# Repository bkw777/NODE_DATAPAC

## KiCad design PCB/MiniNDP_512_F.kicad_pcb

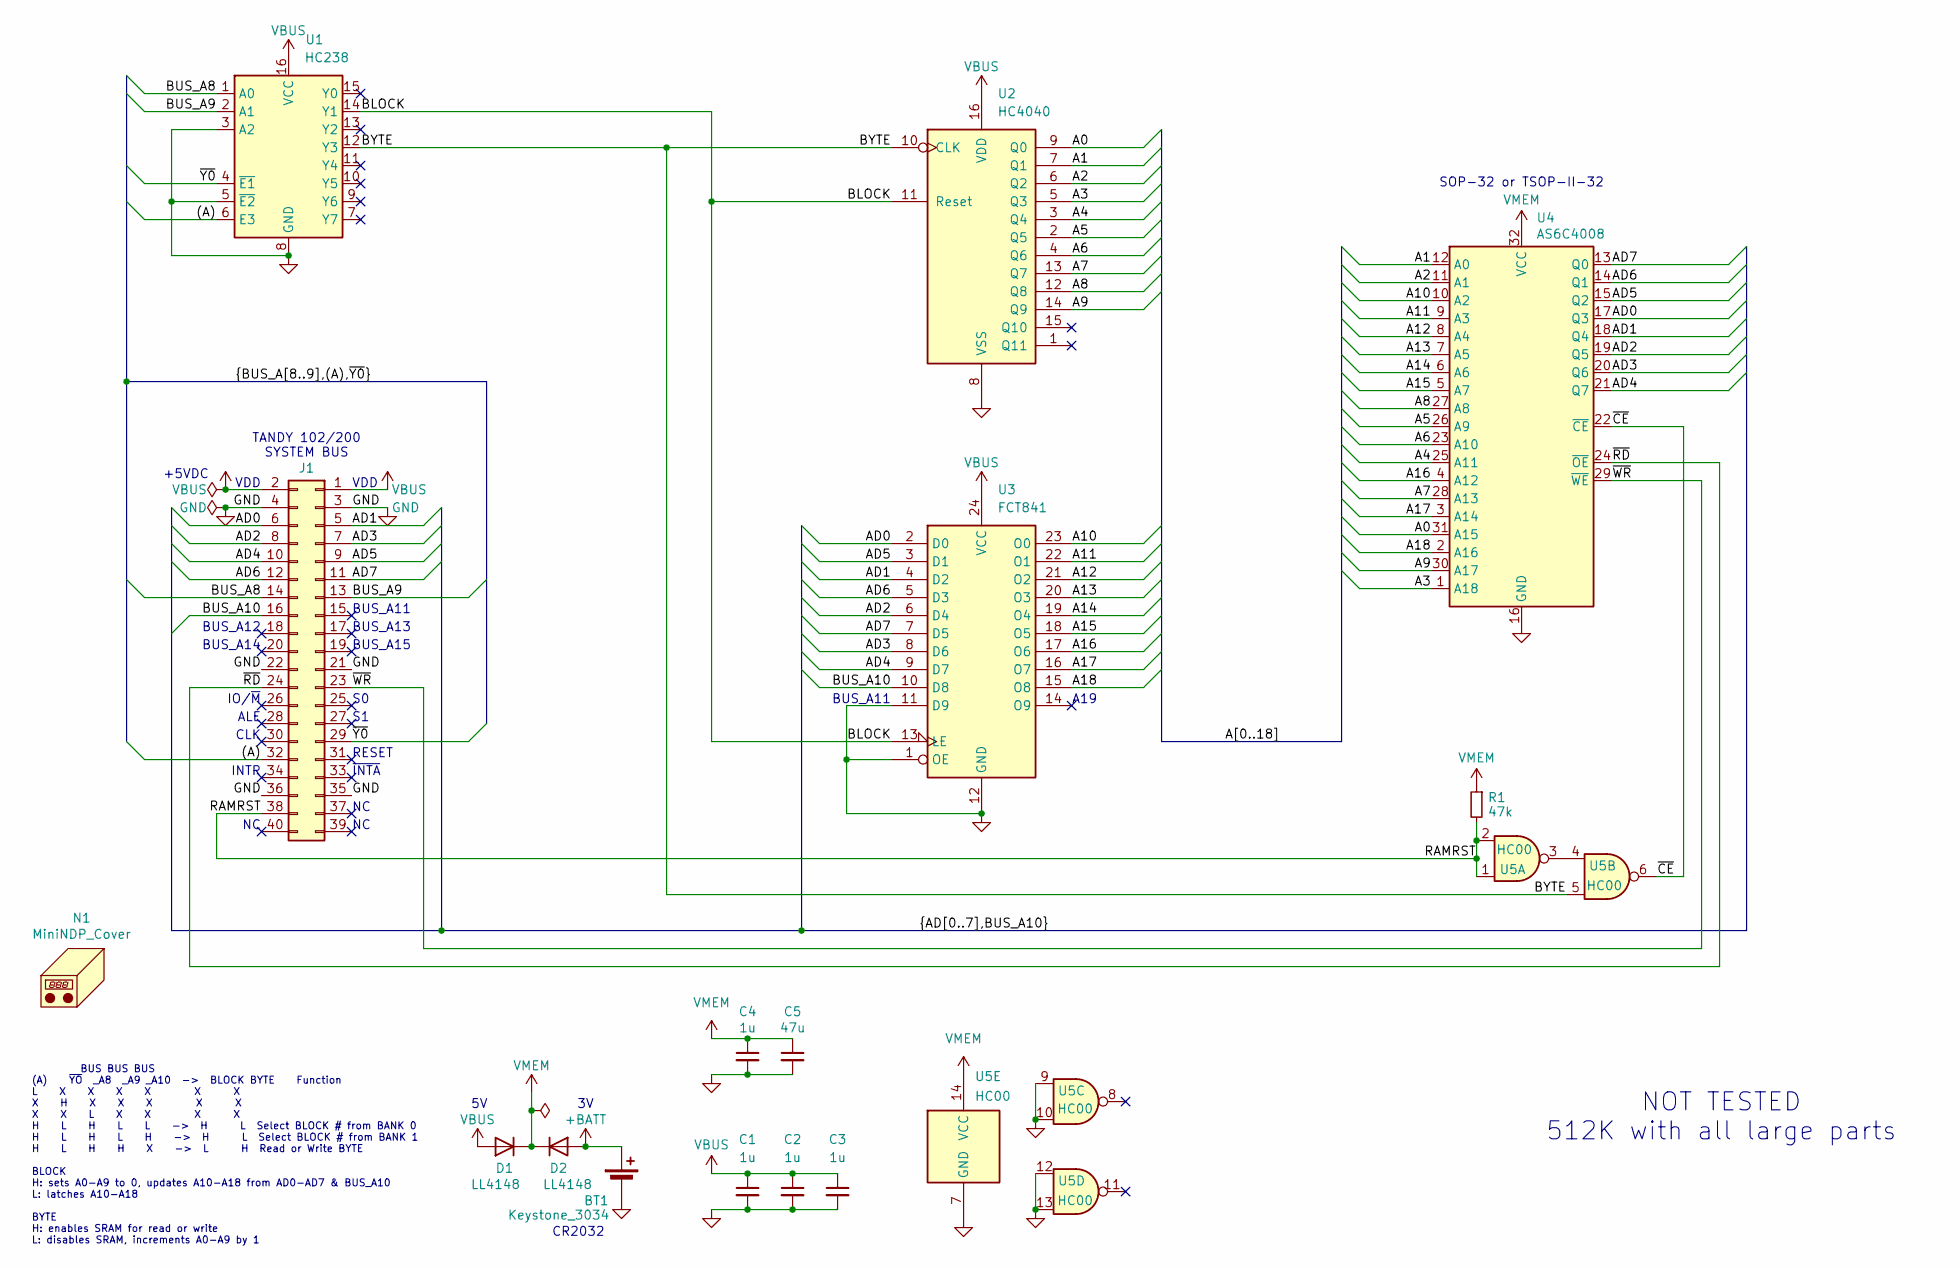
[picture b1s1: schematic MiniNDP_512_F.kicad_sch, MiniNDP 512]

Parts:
BT1: Keystone_3034; Keystone_3028_3034; MPN Keystone 3034
C1, C2, C3, C4: 1u; C_1206; MPN CL31B105KAHNNNE
C5: 47u; C_1206; MPN C3216X5R1E476M160DC
D1, D2: LL4148; D_MiniMELF; MPN FDLL4148
J1: Conn_02x20_Odd_Even; IDC-Header_2x20_P2.54mm_Vertical; MPN 302-S401
N1: MiniNDP_Cover; MPN MiniNDP_Cover.stl
R1: 47k; R_1206; MPN CRGCQ1206F47K
U1: HC238; SOIC-16_3.9x9.9mm_P1.27mm; MPN 74HCT238D,653
U2: HC4040; SOIC-16_3.9x9.9mm_P1.27mm; MPN 74HC4040D,653
U3: FCT841; SOIC-24; MPN CY74FCT841CTSOC
U4: AS6C4008; TSOP-II-SOP-32_dual; MPN AS6C4008-55ZIN
U5: HC00; SOIC-14_3.9x8.7mm_P1.27mm; MPN 74HC00D,653

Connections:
+BATT: BT1.1 (+), D2.2 (A)
/(A): J1.32, U1.6 (E3)
/A0: U2.9 (Q0), U4.31 (A15)
/A1: U2.7 (Q1), U4.12 (A0)
/A2: U2.6 (Q2), U4.11 (A1)
/A3: U2.5 (Q3), U4.1 (A18)
/A4: U2.3 (Q4), U4.25 (A11)
/A5: U2.2 (Q5), U4.26 (A9)
/A6: U2.4 (Q6), U4.23 (A10)
/A7: U2.13 (Q7), U4.28 (A13)
/A8: U2.12 (Q8), U4.27 (A8)
/A9: U2.14 (Q9), U4.30 (A17)
/A10: U3.23 (O0), U4.10 (A2)
/A11: U3.22 (O1), U4.9 (A3)
/A12: U3.21 (O2), U4.8 (A4)
/A13: U3.20 (O3), U4.7 (A5)
/A14: U3.19 (O4), U4.6 (A6)
/A15: U3.18 (O5), U4.5 (A7)
/A16: U3.17 (O6), U4.4 (A12)
/A17: U3.16 (O7), U4.3 (A14)
/A18: U3.15 (O8), U4.2 (A16)
/AD0: J1.6, U3.2 (D0), U4.17 (Q3)
/AD1: J1.5, U3.4 (D2), U4.18 (Q4)
/AD2: J1.8, U3.6 (D4), U4.19 (Q5)
/AD3: J1.7, U3.8 (D6), U4.20 (Q6)
/AD4: J1.10, U3.9 (D7), U4.21 (Q7)
/AD5: J1.9, U3.3 (D1), U4.15 (Q2)
/AD6: J1.12, U3.5 (D3), U4.14 (Q1)
/AD7: J1.11, U3.7 (D5), U4.13 (Q0)
/BLOCK: U1.14 (Y1), U2.11 (Reset), U3.13 (LE)
/BUS_A8: J1.14, U1.1 (A0)
/BUS_A9: J1.13, U1.2 (A1)
/BUS_A10: J1.16, U3.10 (D8)
/BYTE: U1.12 (Y3), U2.10 (CLK), U5.5
/RAMRST: J1.38, R1.2, U5.1, U5.2
/~CE: U4.22 (~CE), U5.6
/~RD: J1.24, U4.24 (~OE)
/~WR: J1.23, U4.29 (~WE)
/~Y0: J1.29, U1.4 (~E1)
GND: BT1.2 (-), C1.2, C2.2, C3.2, C4.2, C5.2, J1.3, J1.4, J1.21, J1.22, J1.35, J1.36, U1.3 (A2), U1.5 (~E2), U1.8 (GND), U2.8 (VSS), U3.1 (OE), U3.11 (D9), U3.12 (GND), U4.16 (GND), U5.7 (GND), U5.9, U5.10, U5.12, U5.13
unnamed: U5.3, U5.4
VBUS: C1.1, C2.1, C3.1, D1.2 (A), J1.1, J1.2, U1.16 (VCC), U2.16 (VDD), U3.24 (VCC)
VMEM: C4.1, C5.1, D1.1 (K), D2.1 (K), R1.1, U4.32 (VCC), U5.14 (VCC)

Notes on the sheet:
BUS_A11
TANDY 102/200 SYSTEM BUS
+5VDC
BUS_A15
NOT TESTED 512K with all large parts
INTR
BUS_A14
ALE
SOP-32 or TSOP-II-32
~{INTA}
CR2032
CLK
IO/~{M}
VDD
RESET
A19
BUS_A13
BUS BUS BUS (A) ~{YO} _A8 _A9 _A10 -> BLOCK BYTE Function L X X X X X X X H X X X X X X X L X X X X H L H L L -> H L Select BLOCK # from BANK 0 H L H L H -> H L Select BLOCK # from BANK 1 H L H H X -> L H Read or Write BYTE BLOCK H: sets A0-A9 to 0, updates A10-A18 from AD0-AD7 & BUS_A10 L: latches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
BUS_A12

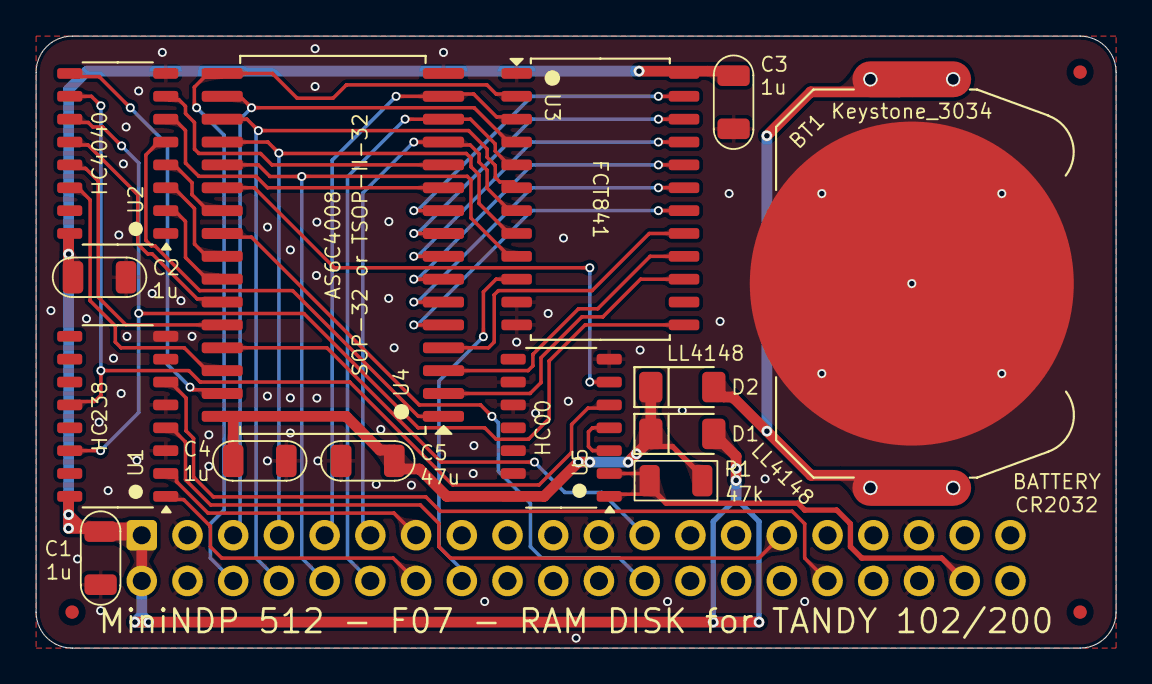
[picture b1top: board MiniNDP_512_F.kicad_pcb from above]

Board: 2 copper layers, 60.0 x 34.0 mm, 19 parts (1 on the bottom side), 43 nets.

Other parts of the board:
F2, F2#2, F3: Fiducial_0.75_1.5

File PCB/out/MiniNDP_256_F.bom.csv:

"Reference","Value","Datasheet","Footprint","Qty","DNP","MPN","Description"
"BT1","Keystone_3034","datasheets/Keystone_3034.pdf","000_LOCAL:Keystone_3028_3034","1","","Keystone 3034","SMT 20mm x 3.2mm coin cell holder"
"C1,C2,C3,C4","1u","datasheets/CL05Y105KP6VPN.pdf","000_LOCAL:C_1206","4","","CL31B105KAHNNNE","CAP CER 1UF 25V X7R 1206"
"C5","47u","datasheets/TDK_MLCC_Cxxxx.pdf","000_LOCAL:C_1206","1","","C3216X5R1E476M160DC","CAP CER 47UF 25V X5R 1206"
"D1,D2","LL4148","datasheets/ll4148.pdf","000_LOCAL:D_MiniMELF","2","","FDLL4148","50V 1A General Purpose Rectifier Diode"
"J1","Conn_02x20_Odd_Even","datasheets/2x20_male_boxed.pdf","000_LOCAL:IDC-Header_2x20_P2.54mm_Vertical","1","","302-S401","CONN HEADER VERT 40POS 2.54MM"
"R1","47k","datasheets/TE-4-2176343-5.pdf","000_LOCAL:R_1206","1","","CRGCQ1206F47K","RES 47K OHM 1% 1/4W 1206"
"U1","HC238","datasheets/HC238.pdf","000_LOCAL:SOIC-16_3.9x9.9mm_P1.27mm","1","","74HC238D,653","IC DECODER/DEMUX 1 X 3:8 16SO"
"U2","HC4040","datasheets/4040.pdf","000_LOCAL:SOIC-16_3.9x9.9mm_P1.27mm","1","","74HC4040D,653","IC BINARY COUNTER 12-BIT 16SO"
"U3","HC573","datasheets/HC573.pdf","000_LOCAL:SOIC-20W_7.5x12.8mm_P1.27mm","1","","74HC573D,653","IC D-TYPE TRANSP SGL 8:8 20SO"
"U4","AS6C2008A","datasheets/AS6C2008A.pdf","000_LOCAL:TSOP-II-SOP-32_dual","1","","AS6C2008A-55SIN","256K x 8 High-Speed CMOS Static RAM, 55/70ns, DIP-32/SOP-32"

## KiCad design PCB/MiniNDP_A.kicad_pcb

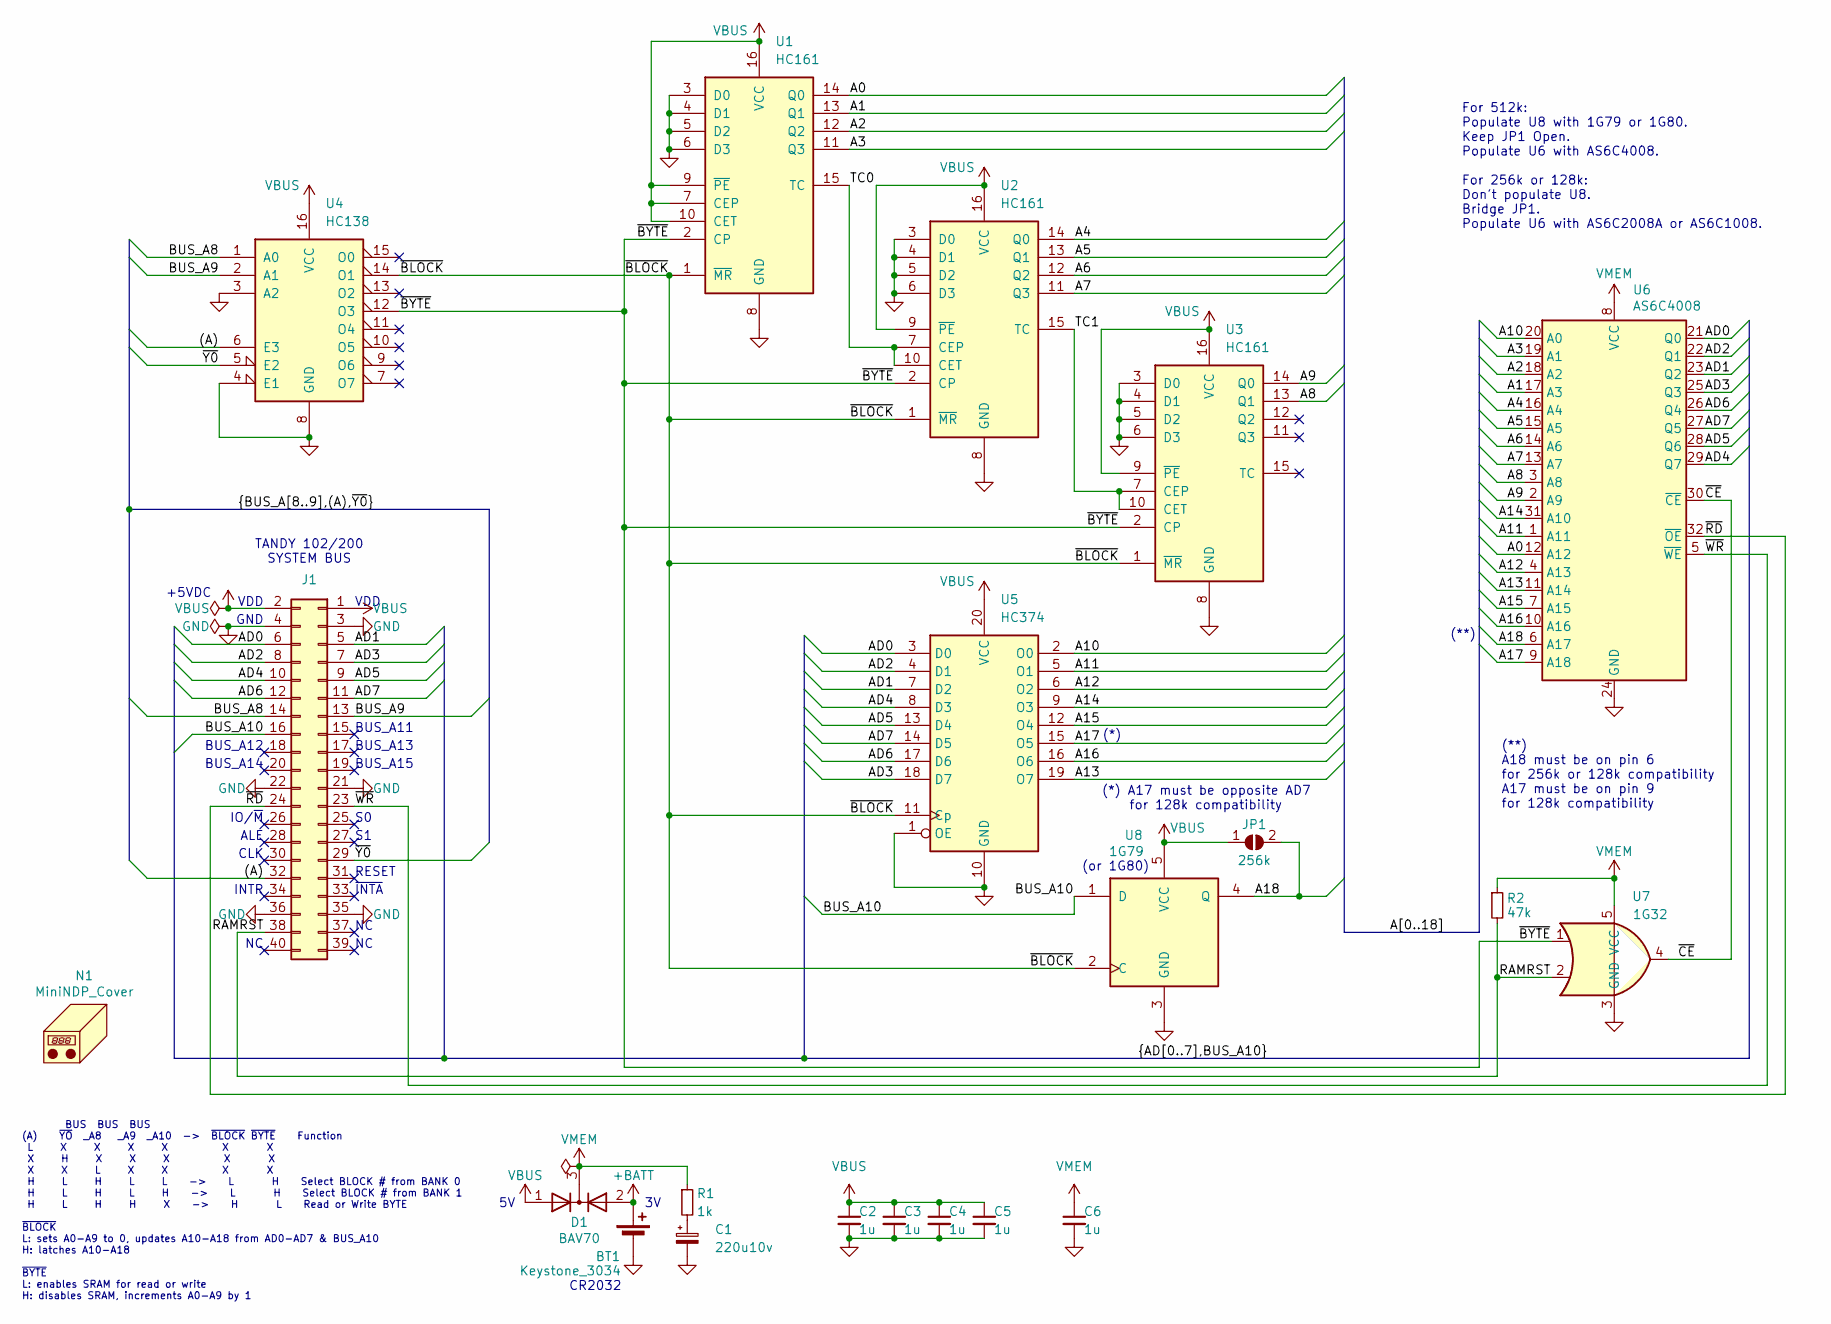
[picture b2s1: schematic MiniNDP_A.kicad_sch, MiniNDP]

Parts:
BT1: Keystone_3034; Keystone_3028_3034; MPN Keystone 3034
C1: 220u10v; CP_6032; MPN TAJC227K010RNJ
C2, C3, C4, C5, C6: 1u; C_0805; MPN CL21B105KAFNNNE
D1: BAV70; SOT-23
J1: Conn_02x20_Odd_Even; IDC-Header_2x20_P2.54mm_Vertical; MPN 302-S401
JP1: 256k; SolderJumper-2_Open 0.65mm
N1: MiniNDP_Cover; MPN MiniNDP_Cover.stl
R1: 1k; R_0805; MPN RK73B2ATTD102J
R2: 47k; R_0805; MPN RMCF0805FT47K0
U1, U2, U3: HC161; TSSOP-16; MPN 74HC161PW,118
U4: HC138; TSSOP-16; MPN 74HC138PW,118
U5: HC374; TSSOP-20; MPN 74HC374PW,118
U6: AS6C4008; TSOP32-dual; MPN AS6C4008-55STIN
U7: 1G32; SOT-353_SC-70-5; MPN 74LVC1G32GW,125
U8: 1G79; SOT-353_SC-70-5; MPN 74LVC1G79GW,125

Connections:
+BATT: BT1.1 (+), D1.2 (A)
/(A): J1.32, U4.6 (E3)
/A0: U1.14 (Q0), U6.12 (A12)
/A1: U1.13 (Q1), U6.17 (A3)
/A2: U1.12 (Q2), U6.18 (A2)
/A3: U1.11 (Q3), U6.19 (A1)
/A4: U2.14 (Q0), U6.16 (A4)
/A5: U2.13 (Q1), U6.15 (A5)
/A6: U2.12 (Q2), U6.14 (A6)
/A7: U2.11 (Q3), U6.13 (A7)
/A8: U3.13 (Q1), U6.3 (A8)
/A9: U3.14 (Q0), U6.2 (A9)
/A10: U5.2 (O0), U6.20 (A0)
/A11: U5.5 (O1), U6.1 (A11)
/A12: U5.6 (O2), U6.4 (A13)
/A13: U5.19 (O7), U6.11 (A14)
/A14: U5.9 (O3), U6.31 (A10)
/A15: U5.12 (O4), U6.7 (A15)
/A16: U5.16 (O6), U6.10 (A16)
/A17: U5.15 (O5), U6.9 (A18)
/A18: JP1.2 (B), U6.6 (A17), U8.4 (Q)
/AD0: J1.6, U5.3 (D0), U6.21 (Q0)
/AD1: J1.5, U5.7 (D2), U6.23 (Q2)
/AD2: J1.8, U5.4 (D1), U6.22 (Q1)
/AD3: J1.7, U5.18 (D7), U6.25 (Q3)
/AD4: J1.10, U5.8 (D3), U6.29 (Q7)
/AD5: J1.9, U5.13 (D4), U6.28 (Q6)
/AD6: J1.12, U5.17 (D6), U6.26 (Q4)
/AD7: J1.11, U5.14 (D5), U6.27 (Q5)
/BUS_A8: J1.14, U4.1 (A0)
/BUS_A9: J1.13, U4.2 (A1)
/BUS_A10: J1.16, U8.1 (D)
/RAMRST: J1.38, R2.2, U7.2
/TC0: U1.15 (TC), U2.7 (CEP), U2.10 (CET)
/TC1: U2.15 (TC), U3.7 (CEP), U3.10 (CET)
/~BLOCK: U1.1 (~MR), U2.1 (~MR), U3.1 (~MR), U4.14 (O1), U5.11 (Cp), U8.2 (C)
/~BYTE: U1.2 (CP), U2.2 (CP), U3.2 (CP), U4.12 (O3), U7.1
/~CE: U6.30 (~CE), U7.4
/~RD: J1.24, U6.32 (~OE)
/~WR: J1.23, U6.5 (~WE); also elsewhere on the board
/~Y0: J1.29, U4.5 (E2)
GND: BT1.2 (-), C1.2, C2.2, C3.2, C4.2, C5.2, C6.2, J1.3, J1.4, J1.21, J1.22, J1.35, J1.36, U1.3 (D0), U1.4 (D1), U1.5 (D2), U1.6 (D3), U1.8 (GND), U2.3 (D0), U2.4 (D1), U2.5 (D2), U2.6 (D3), U2.8 (GND), U3.3 (D0), U3.4 (D1), U3.5 (D2), U3.6 (D3), U3.8 (GND), U4.3 (A2), U4.4 (E1), U4.8 (GND), U5.1 (OE), U5.10 (GND), U6.24 (GND), U7.3 (GND), U8.3 (GND)
unnamed: C1.1, R1.2
VBUS: C2.1, C3.1, C4.1, C5.1, D1.1 (A), J1.1, J1.2, JP1.1 (A), U1.7 (CEP), U1.9 (~PE), U1.10 (CET), U1.16 (VCC), U2.9 (~PE), U2.16 (VCC), U3.9 (~PE), U3.16 (VCC), U4.16 (VCC), U5.20 (VCC), U8.5 (VCC)
VMEM: C6.1, D1.3 (K), R1.1, R2.1, U6.8 (VCC), U7.5 (VCC); also elsewhere on the board

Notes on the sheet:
TANDY 102/200 SYSTEM BUS
+5VDC
BUS_A15
INTR
BUS_A14
ALE
~{INTA}
CLK
(**) A18 must be on pin 6 for 256k or 128k compatibility A17 must be on pin 9 for 128k compatibility
GND
For 512k: Populate U8 with 1G79 or 1G80. Keep JP1 Open. Populate U6 with AS6C4008. For 256k or 128k: Don't populate U8. Bridge JP1. Populate U6 with AS6C2008A or AS6C1008.
IO/~{M}
CR2032
VDD
(or 1G80)
BUS BUS BUS (A) ~{YO} _A8 _A9 _A10 -> ~{BLOCK} ~{BYTE} Function L X X X X X X X H X X X X X X X L X X X X H L H L L -> L H Select BLOCK # from BANK 0 H L H L H -> L H Select BLOCK # from BANK 1 H L H H X -> H L Read or Write BYTE ~{BLOCK} L: sets A0-A9 to 0, updates A10-A18 from AD0-AD7 & BUS_A10 H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
RESET
(*) A17 must be opposite AD7 for 128k compatibility
(**)
BUS_A11
BUS_A13
(*)
BUS_A12

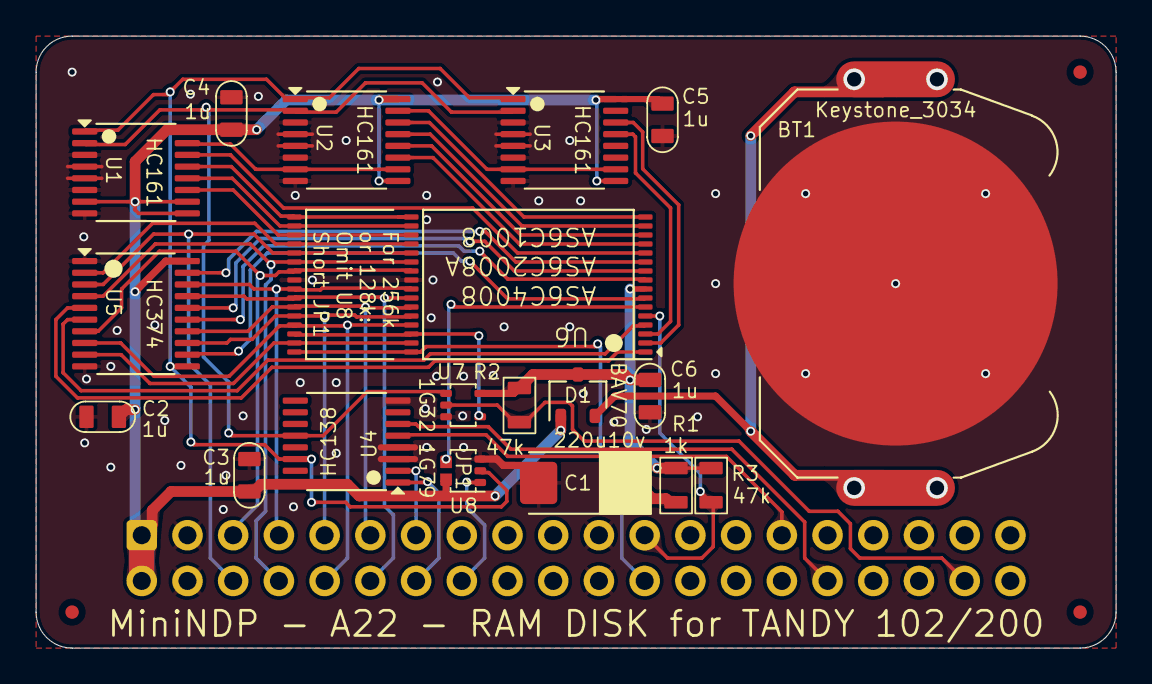
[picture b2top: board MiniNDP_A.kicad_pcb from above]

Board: 2 copper layers, 60.0 x 34.0 mm, 25 parts (1 on the bottom side), 45 nets.

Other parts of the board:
F3, F3#2, F3#3: Fiducial_0.75_1.5
R3: 47k; R_0805

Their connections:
/~WR: R3.2; also elsewhere on the board
VMEM: R3.1; also elsewhere on the board

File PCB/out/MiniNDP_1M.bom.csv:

"Reference","Value","Datasheet","Footprint","Qty","DNP","MPN","Description"
"BT1","Keystone_3034","datasheets/Keystone_3034.pdf","000_LOCAL:Keystone_3028_3034","1","","Keystone 3034","SMT 20mm x 3.2mm coin cell holder"
"C1","220u10v","datasheets/TAJ.odf","000_LOCAL:CP_6032","1","","TAJC227K010RNJ","CAP TANT 220UF 10% 10V 2312"
"C2,C3,C4,C5","1u","datasheets/CL21B105KAFNNNE.pdf","000_LOCAL:C_0805","4","","CL21B105KAFNNNE","CAP CER 1UF 25V X7R 0805"
"DA1","BAS70DW-05","datasheets/BAS70.pdf","000_LOCAL:SOT-363_SC-70-6_symmetric","1","","BAS70DW-05-7-F","DIODE ARR SCHOTT 70V 70MA SOT363 2-PAIR COMMON-CATHODE"
"J1","Conn_02x20_Odd_Even","datasheets/2x20_male_boxed.pdf","000_LOCAL:IDC-Header_2x20_P2.54mm_Vertical","1","","302-S401","CONN HEADER VERT 40POS 2.54MM"
"R1","1k","datasheets/RK73.pdf","000_LOCAL:R_0805","1","","RK73B2ATTD102J","RES 1K OHM 5% 1/4W 0805"
"R2","47k","datasheets/sei-rmcf_rmcp.pdf","000_LOCAL:R_0805","1","","RMCF0805FT47K0","RES 47K OHM 1% 1/8W 0805"
"U1,U2,U3","HC161","datasheets/HC161.pdf","000_LOCAL:TSSOP-16","3","","74HC161PW,118","IC BINARY COUNTER 4-BIT 16TSSOP"
"U4","HC138","datasheets/HC138.pdf","000_LOCAL:TSSOP-16","1","","74HC138PW,118","IC DECODER/DEMUX 1X3:8 16TSSOP"
"U5","FCT821","datasheets/CY74FCT821T.pdf","000_LOCAL:SOIC-24","1","","CY74FCT821BTSOC","IC FF D-TYPE SNGL 10BIT 24SOIC"
"U6","AS6C8008_TSOPII","datasheets/AS6C8008.pdf","000_LOCAL:TSOP-II-44","1","","AS6C8008-55ZIN","IC SRAM 1Mx8 PARALLEL 5v TSOP-II-44"
"U7","1G32","datasheets/LVC1G32.pdf","000_LOCAL:SOT-353_SC-70-5","1","","74LVC1G32GW,125","IC GATE OR 1CH 2-INP 5TSSOP"

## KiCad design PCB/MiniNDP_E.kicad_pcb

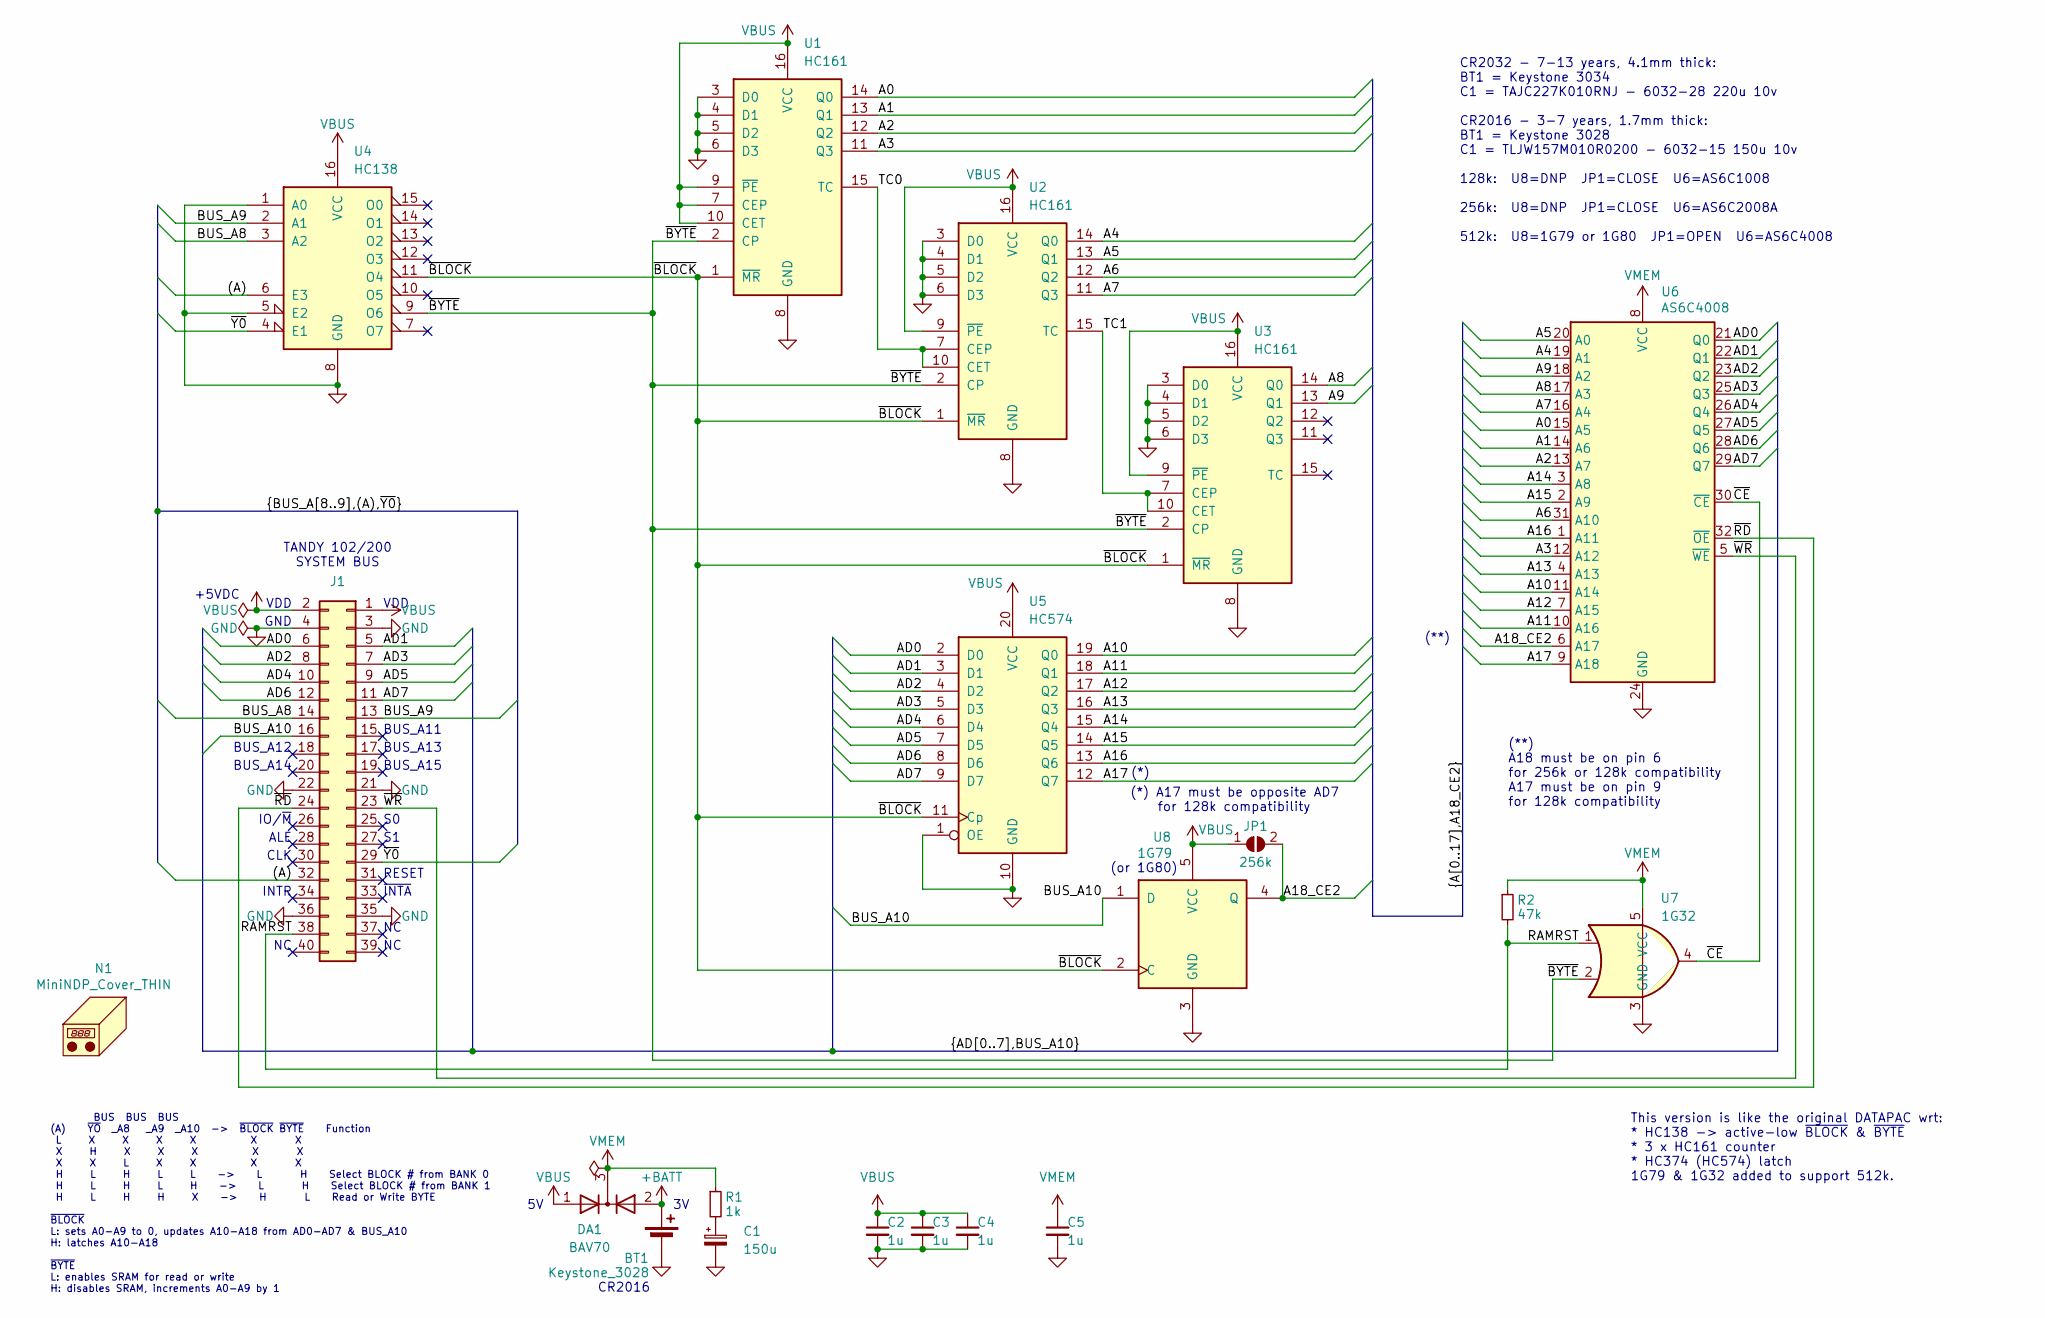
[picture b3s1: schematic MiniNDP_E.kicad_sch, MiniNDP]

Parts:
BT1: Keystone_3028; Keystone_3028_3034; MPN Keystone_3028
C1: 150u; CP_6032; MPN TLJW157M010R0200
C2, C3, C4, C5: 1u; C_0805; MPN CL21B105KAFNNNE
DA1: BAV70; SOT-23; MPN BAV70-7-F
J1: Conn_02x20_Odd_Even; IDC-Header_2x20_P2.54mm_Vertical; MPN 302-S401
JP1: 256k; SolderJumper-2_Open 0.65mm
N1: MiniNDP_Cover_THIN; MPN MiniNDP_Cover_THIN.stl
R1: 1k; R_0805; MPN RK73B2ATTD102J
R2: 47k; R_0805; MPN RMCF0805FT47K0
U1, U2, U3: HC161; TSSOP-16; MPN 74HC161PW,118
U4: HC138; TSSOP-16; MPN 74HC138PW,118
U5: HC574; TSSOP-20; MPN 74HC574PW,118
U6: AS6C4008; TSOP32-dual; MPN AS6C4008-55STIN
U7: 1G32; SOT-353_SC-70-5; MPN 74LVC1G32GW,125
U8: 1G79; SOT-353_SC-70-5; MPN 74LVC1G79GW,125

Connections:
+BATT: BT1.1 (+), DA1.2 (A)
/(A): J1.32, U4.6 (E3)
/A0: U1.14 (Q0), U6.15 (A5)
/A1: U1.13 (Q1), U6.14 (A6)
/A2: U1.12 (Q2), U6.13 (A7)
/A3: U1.11 (Q3), U6.12 (A12)
/A4: U2.14 (Q0), U6.19 (A1)
/A5: U2.13 (Q1), U6.20 (A0)
/A6: U2.12 (Q2), U6.31 (A10)
/A7: U2.11 (Q3), U6.16 (A4)
/A8: U3.14 (Q0), U6.17 (A3)
/A9: U3.13 (Q1), U6.18 (A2)
/A10: U5.19 (Q0), U6.11 (A14)
/A11: U5.18 (Q1), U6.10 (A16)
/A12: U5.17 (Q2), U6.7 (A15)
/A13: U5.16 (Q3), U6.4 (A13)
/A14: U5.15 (Q4), U6.3 (A8)
/A15: U5.14 (Q5), U6.2 (A9)
/A16: U5.13 (Q6), U6.1 (A11)
/A17: U5.12 (Q7), U6.9 (A18)
/A18_CE2: JP1.2 (B), U6.6 (A17), U8.4 (Q)
/AD0: J1.6, U5.2 (D0), U6.21 (Q0)
/AD1: J1.5, U5.3 (D1), U6.22 (Q1)
/AD2: J1.8, U5.4 (D2), U6.23 (Q2)
/AD3: J1.7, U5.5 (D3), U6.25 (Q3)
/AD4: J1.10, U5.6 (D4), U6.26 (Q4)
/AD5: J1.9, U5.7 (D5), U6.27 (Q5)
/AD6: J1.12, U5.8 (D6), U6.28 (Q6)
/AD7: J1.11, U5.9 (D7), U6.29 (Q7)
/BUS_A8: J1.14, U4.3 (A2)
/BUS_A9: J1.13, U4.2 (A1)
/BUS_A10: J1.16, U8.1 (D)
/RAMRST: J1.38, R2.2, U7.1
/TC0: U1.15 (TC), U2.7 (CEP), U2.10 (CET)
/TC1: U2.15 (TC), U3.7 (CEP), U3.10 (CET)
/~BLOCK: U1.1 (~MR), U2.1 (~MR), U3.1 (~MR), U4.11 (O4), U5.11 (Cp), U8.2 (C)
/~BYTE: U1.2 (CP), U2.2 (CP), U3.2 (CP), U4.9 (O6), U7.2
/~CE: U6.30 (~CE), U7.4
/~RD: J1.24, U6.32 (~OE)
/~WR: J1.23, U6.5 (~WE)
/~Y0: J1.29, U4.4 (E1)
GND: BT1.2 (-), C1.2, C2.2, C3.2, C4.2, C5.2, J1.3, J1.4, J1.21, J1.22, J1.35, J1.36, U1.3 (D0), U1.4 (D1), U1.5 (D2), U1.6 (D3), U1.8 (GND), U2.3 (D0), U2.4 (D1), U2.5 (D2), U2.6 (D3), U2.8 (GND), U3.3 (D0), U3.4 (D1), U3.5 (D2), U3.6 (D3), U3.8 (GND), U4.1 (A0), U4.5 (E2), U4.8 (GND), U5.1 (OE), U5.10 (GND), U6.24 (GND), U7.3 (GND), U8.3 (GND)
unnamed: C1.1, R1.2
VBUS: C2.1, C3.1, C4.1, DA1.1 (A), J1.1, J1.2, JP1.1 (A), U1.7 (CEP), U1.9 (~PE), U1.10 (CET), U1.16 (VCC), U2.9 (~PE), U2.16 (VCC), U3.9 (~PE), U3.16 (VCC), U4.16 (VCC), U5.20 (VCC), U8.5 (VCC)
VMEM: C5.1, DA1.3 (K), R1.1, R2.1, U6.8 (VCC), U7.5 (VCC)

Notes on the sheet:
TANDY 102/200 SYSTEM BUS
+5VDC
BUS_A15
INTR
BUS_A14
ALE
~{INTA}
CLK
(**) A18 must be on pin 6 for 256k or 128k compatibility A17 must be on pin 9 for 128k compatibility
CR2032 - 7-13 years, 4.1mm thick: BT1 = Keystone 3034 C1 = TAJC227K010RNJ - 6032-28 220u 10v CR2016 - 3-7 years, 1.7mm thick: BT1 = Keystone 3028 C1 = TLJW157M010R0200 - 6032-15 150u 10v 128k: U8=DNP JP1=CLOSE U6=AS6C1008 256k: U8=DNP JP1=CLOSE U6=AS6C2008A 512k: U8=1G79 or 1G80 JP1=OPEN U6=AS6C4008
GND
IO/~{M}
CR2016
(or 1G80)
VDD
BUS BUS BUS (A) ~{YO} _A8 _A9 _A10 -> ~{BLOCK} ~{BYTE} Function L X X X X X X X H X X X X X X X L X X X X H L H L L -> L H Select BLOCK # from BANK 0 H L H L H -> L H Select BLOCK # from BANK 1 H L H H X -> H L Read or Write BYTE ~{BLOCK} L: sets A0-A9 to 0, updates A10-A18 from AD0-AD7 & BUS_A10 H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
RESET
(*) A17 must be opposite AD7 for 128k compatibility
This version is like the original DATAPAC wrt: * HC138 -> active-low ~{BLOCK} & ~{BYTE} * 3 x HC161 counter * HC374 (HC574) latch 1G79 & 1G32 added to support 512k.
(**)
BUS_A11
BUS_A13
(*)
BUS_A12

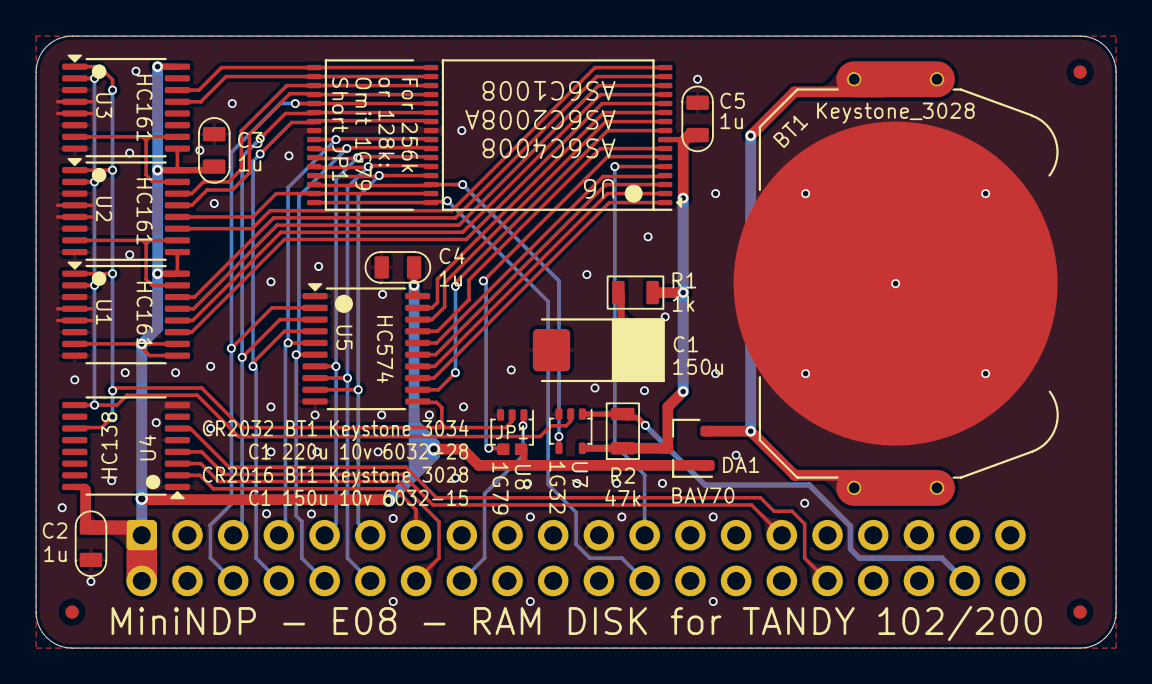
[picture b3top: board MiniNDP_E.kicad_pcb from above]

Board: 2 copper layers, 60.0 x 34.0 mm, 23 parts (1 on the bottom side), 45 nets.

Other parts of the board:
F3, F3#2, F3#3: Fiducial_0.75_1.5

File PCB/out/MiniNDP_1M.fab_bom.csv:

"Reference","Value","Datasheet","Footprint","Qty","DNP","MPN","Description"
"BT1","Keystone_3034","datasheets/Keystone_3034.pdf","000_LOCAL:Keystone_3028_3034","1","","Keystone 3034","SMT 20mm x 3.2mm coin cell holder"
"C1","220u10v","datasheets/TAJ.odf","000_LOCAL:CP_6032","1","","TAJC227K010RNJ","CAP TANT 220UF 10% 10V 2312"
"C2,C3,C4,C5","1u","datasheets/CL21B105KAFNNNE.pdf","000_LOCAL:C_0805","4","","CL21B105KAFNNNE","CAP CER 1UF 25V X7R 0805"
"DA1","BAS70DW-05","datasheets/BAS70.pdf","000_LOCAL:SOT-363_SC-70-6_symmetric","1","","BAS70DW-05-7-F","DIODE ARR SCHOTT 70V 70MA SOT363 2-PAIR COMMON-CATHODE"
"J1","Conn_02x20_Odd_Even","datasheets/2x20_male_boxed.pdf","000_LOCAL:IDC-Header_2x20_P2.54mm_Vertical","1","","302-S401","CONN HEADER VERT 40POS 2.54MM"
"R1","1k","datasheets/RK73.pdf","000_LOCAL:R_0805","1","","RK73B2ATTD102J","RES 1K OHM 5% 1/4W 0805"
"R2,R3","47k","-- mixed values --","000_LOCAL:R_0805","2","","RMCF0805FT47K0","RES 47K OHM 1% 1/8W 0805"
"U1,U2,U3","HC161","datasheets/HC161.pdf","000_LOCAL:TSSOP-16","3","","74HC161PW,118","IC BINARY COUNTER 4-BIT 16TSSOP"
"U4","HC138","datasheets/HC138.pdf","000_LOCAL:TSSOP-16","1","","74HC138PW,118","IC DECODER/DEMUX 1X3:8 16TSSOP"
"U5","FCT821","datasheets/CY74FCT821T.pdf","000_LOCAL:SOIC-24","1","","CY74FCT821BTSOC","IC FF D-TYPE SNGL 10BIT 24SOIC"
"U6","AS6C8008_TSOPII","datasheets/AS6C8008.pdf","000_LOCAL:TSOP-II-44","1","","AS6C8008-55ZIN","IC SRAM 1Mx8 PARALLEL TSOP-II-44"
"U7","1G32","datasheets/LVC1G32.pdf","000_LOCAL:SOT-353_SC-70-5","1","","74LVC1G32GW,125","IC GATE OR 1CH 2-INP 5TSSOP"

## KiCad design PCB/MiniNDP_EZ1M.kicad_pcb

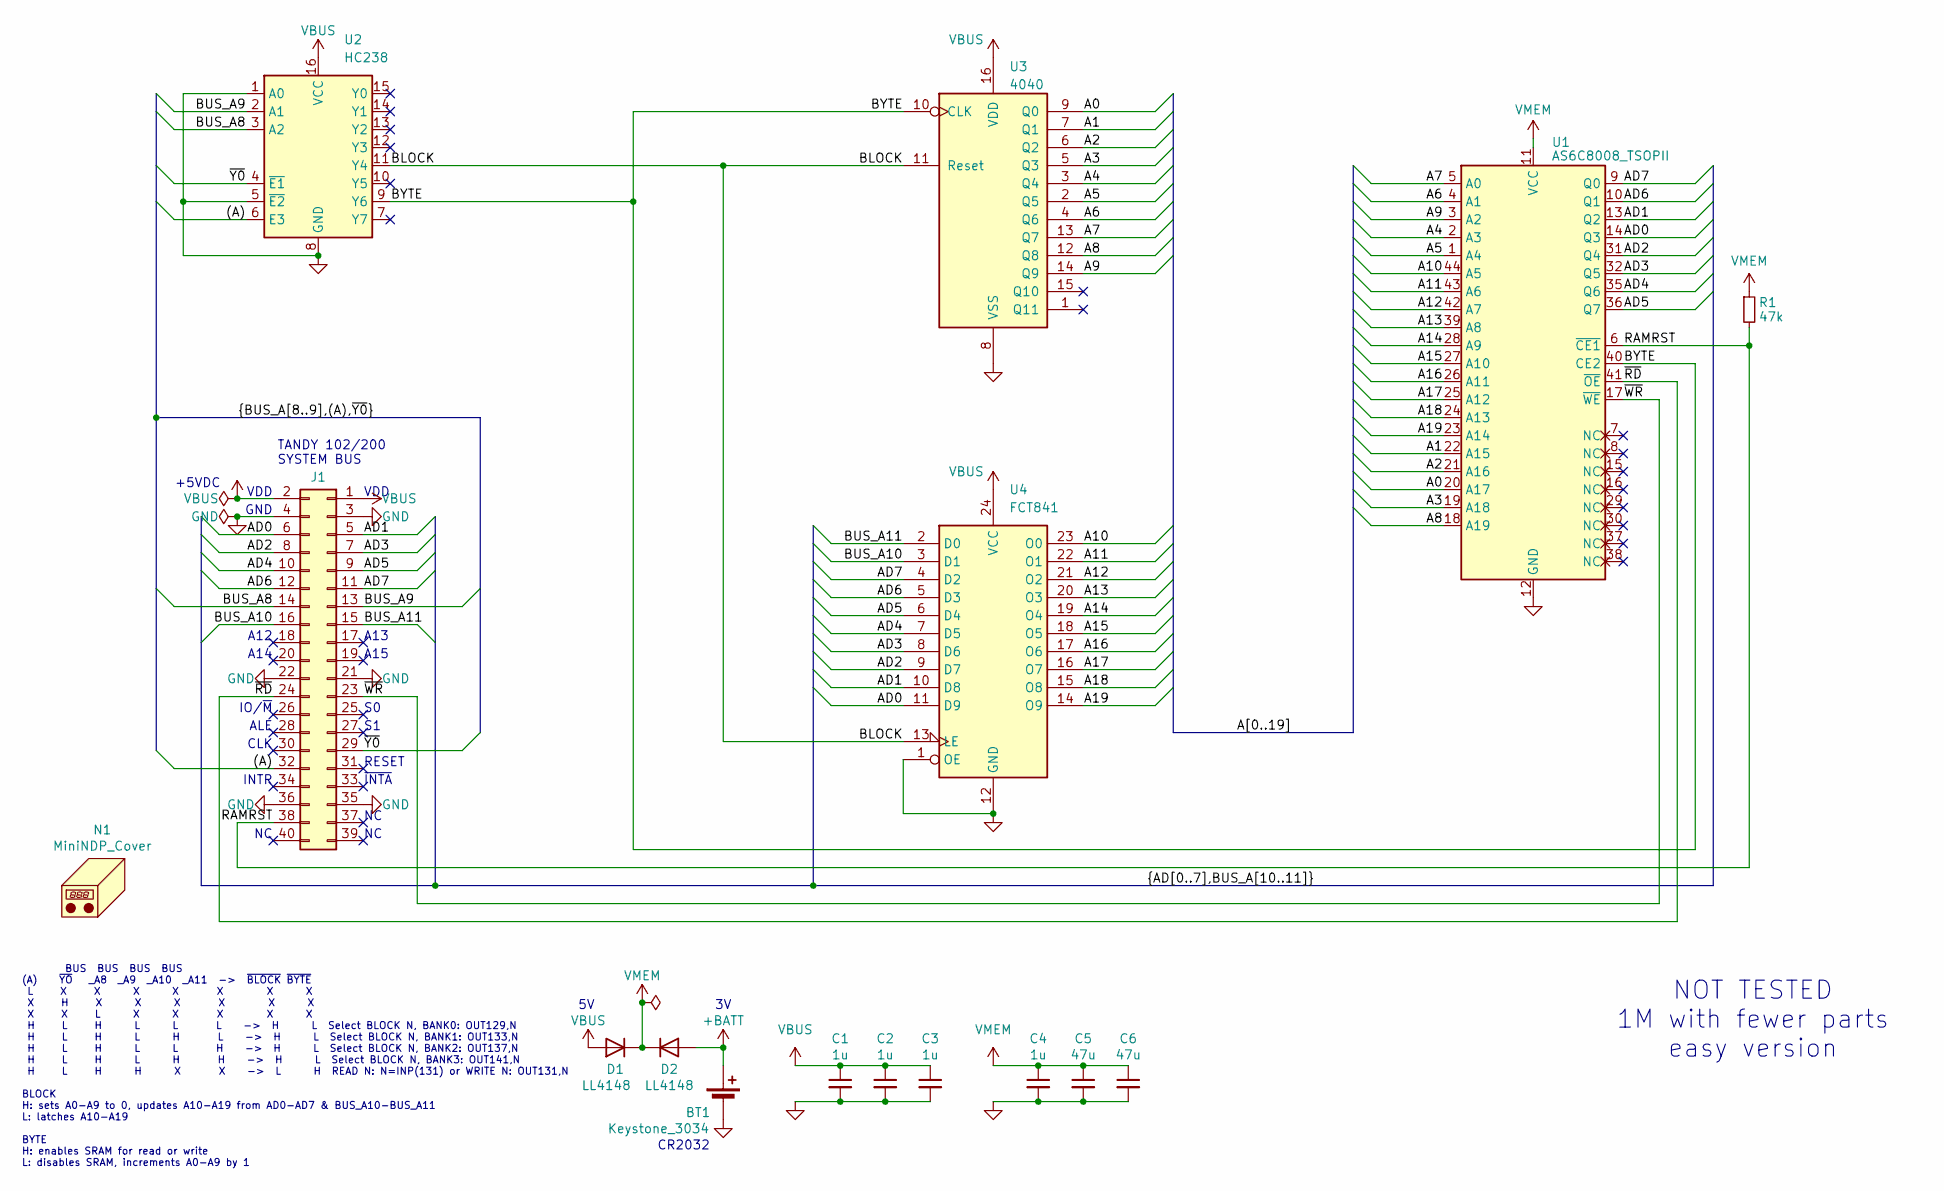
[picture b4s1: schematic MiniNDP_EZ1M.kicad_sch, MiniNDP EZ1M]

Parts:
BT1: Keystone_3034; Keystone_3028_3034; MPN Keystone 3034
C1, C2, C3, C4: 1u; C_0805; MPN CL21B105KAFNNNE
C5, C6: 47u; C_1206; MPN C3216X5R1E476M160DC
D1, D2: LL4148; D_MiniMELF; MPN FDLL4148
J1: Conn_02x20_Odd_Even; IDC-Header_2x20_P2.54mm_Vertical; MPN 302-S401
N1: MiniNDP_Cover; MPN MiniNDP_Cover.stl
R1: 47k; R_0805; MPN RMCF0805FT47K0
U1: AS6C8008_TSOPII; TSOP-II-44; MPN AS6C8008-55ZIN
U2: HC238; SOIC-16_3.9x9.9mm_P1.27mm; MPN 74HC238D,653
U3: 4040; SOIC-16_3.9x9.9mm_P1.27mm; MPN 74HC4040D,653
U4: FCT841; SOIC-24; MPN CY74FCT841CTSOC

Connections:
+BATT: BT1.1 (+), D2.2 (A)
/(A): J1.32, U2.6 (E3)
/A0: U1.20 (A17), U3.9 (Q0)
/A1: U1.22 (A15), U3.7 (Q1)
/A2: U1.21 (A16), U3.6 (Q2)
/A3: U1.19 (A18), U3.5 (Q3)
/A4: U1.2 (A3), U3.3 (Q4)
/A5: U1.1 (A4), U3.2 (Q5)
/A6: U1.4 (A1), U3.4 (Q6)
/A7: U1.5 (A0), U3.13 (Q7)
/A8: U1.18 (A19), U3.12 (Q8)
/A9: U1.3 (A2), U3.14 (Q9)
/A10: U1.44 (A5), U4.23 (O0)
/A11: U1.43 (A6), U4.22 (O1)
/A12: U1.42 (A7), U4.21 (O2)
/A13: U1.39 (A8), U4.20 (O3)
/A14: U1.28 (A9), U4.19 (O4)
/A15: U1.27 (A10), U4.18 (O5)
/A16: U1.26 (A11), U4.17 (O6)
/A17: U1.25 (A12), U4.16 (O7)
/A18: U1.24 (A13), U4.15 (O8)
/A19: U1.23 (A14), U4.14 (O9)
/AD0: J1.6, U1.14 (Q3), U4.11 (D9)
/AD1: J1.5, U1.13 (Q2), U4.10 (D8)
/AD2: J1.8, U1.31 (Q4), U4.9 (D7)
/AD3: J1.7, U1.32 (Q5), U4.8 (D6)
/AD4: J1.10, U1.35 (Q6), U4.7 (D5)
/AD5: J1.9, U1.36 (Q7), U4.6 (D4)
/AD6: J1.12, U1.10 (Q1), U4.5 (D3)
/AD7: J1.11, U1.9 (Q0), U4.4 (D2)
/BLOCK: U2.11 (Y4), U3.11 (Reset), U4.13 (LE)
/BUS_A8: J1.14, U2.3 (A2)
/BUS_A9: J1.13, U2.2 (A1)
/BUS_A10: J1.16, U4.3 (D1)
/BUS_A11: J1.15, U4.2 (D0)
/BYTE: U1.40 (CE2), U2.9 (Y6), U3.10 (CLK)
/RAMRST: J1.38, R1.2, U1.6 (~CE1)
/~RD: J1.24, U1.41 (~OE)
/~WR: J1.23, U1.17 (~WE)
/~Y0: J1.29, U2.4 (~E1)
GND: BT1.2 (-), C1.2, C2.2, C3.2, C4.2, C5.2, C6.2, J1.3, J1.4, J1.21, J1.22, J1.35, J1.36, U1.12 (GND), U1.34 (GND), U2.1 (A0), U2.5 (~E2), U2.8 (GND), U3.8 (VSS), U4.1 (OE), U4.12 (GND)
VBUS: C1.1, C2.1, C3.1, D1.2 (A), J1.1, J1.2, U2.16 (VCC), U3.16 (VDD), U4.24 (VCC)
VMEM: C4.1, C5.1, C6.1, D1.1 (K), D2.1 (K), R1.1, U1.11 (VCC), U1.33 (VCC)

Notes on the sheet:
TANDY 102/200 SYSTEM BUS
+5VDC
A15
CR2032
INTR
A14
ALE
~{INTA}
CLK
GND
IO/~{M}
VDD
BUS BUS BUS BUS (A) ~{YO} _A8 _A9 _A10 _A11 -> ~{BLOCK} ~{BYTE} L X X X X X X X X H X X X X X X X X L X X X X X H L H L L L -> H L Select BLOCK N, BANK0: OUT129,N H L H L H L -> H L Select BLOCK N, BANK1: OUT133,N H L H L L H -> H L Select BLOCK N, BANK2: OUT137,N H L H L H H -> H L Select BLOCK N,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
RESET
A13
A12
NOT TESTED 1M with fewer parts easy version
